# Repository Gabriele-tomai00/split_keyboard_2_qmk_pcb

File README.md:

# SPLIT KEYBOARD (my second version)

<!-- ## ⚠️ Report In Progress ⚠️ -->
This project details the design and construction of my first custom split keyboard. The build features a custom PCB, hand-soldered components, and a 3D-printed case, all powered by the Raspberry Pi Pico and QMK firmware.

**Key Features:**
- **Microcontroller**: Raspberry Pi Pico (RP2040)
- **Firmware**: QMK with Vial GUI support
- **Switches**: Hot-swappable MX switches
- **Displays**: OLED status screens
- **Input**: Rotary encoders
- **Interconnect**: RJ11 cabling for safe hot-plugging

The layout is a traditional row-staggered design (non-ortholinear) with ergonomic enhancements:
- **Inner Macro Keys**: 3 extra keys on the inner side of the right half.
- **Thumb Cluster**: 2 low-profile keys under each spacebar, primarily used as layer modifiers.

*Acknowledgments: Special thanks to the QMK and Vial communities, and the authors of the Sofle Pico keyboard, whose work provided invaluable inspiration and knowledge.*

## Repository Structure
- `/3d_images`: 3D design files (STL) created with Autodesk Fusion 360
- `/images`: Photographic documentation of the keyboard assembly and final build.
- `/kicad`: Electrical schematics and PCB layout designs developed in KiCad, ready for fabrication.
- `/vial-qmk`: Source code for the QMK-based firmware with Vial GUI support.
- `/vial_config.vil`: Vial configuration file (you can upload this file to Vial to configure the keyboard).
- `/perimeter_right.dxf` and `/perimeter_left.dxf`: DXF files for the right and left half PCB perimeter (used to cut the PCB).

## Components List
- Custom PCBs (Left & Right)
- 2x Raspberry Pi Pico
- 1N4148 Diodes
- Kailh Hot-swap Sockets
- SK6812MINI-E SMD LEDs
- EC11 Rotary Encoders
- 0.91" I2C OLED Displays
- RJ11 Jacks (6P6C or similar)
- Brass Standoffs (M2)

## Features & Implementation

### Layout & Ergonomics
The keyboard deviates slightly from a standard 60% ANSI layout to accommodate split ergonomics. It combines standard MX switches with low-profile switches for the thumb cluster to reduce strain. The extra macro keys on the left half provide quick access to custom functions.

### Software (QMK & Vial)
The keyboard runs on QMK firmware and is fully compatible with Vial. This allows for real-time configuration via a graphical interface without re-flashing. Users can program:
- **Layers**: Toggle between different keymaps (e.g., QWERTY, navigation, numpad).
- **Macros**: Automate complex key sequences.
- **Tap Dance**: Assign different actions to a key based on how many times it is tapped.

### Rotary Encoders (EC11)
The keyboard utilizes EC11 rotary encoders. In the QMK ecosystem, encoders provide a fluid input method distinct from binary key presses. They are ideal for continuous values like volume control, page scrolling, or history navigation.

### OLED Displays
Each half is equipped with an OLED display connected via the I2C protocol.

### RGB Backlighting (SK6812MINI-E)
The PCB features per-key RGB backlighting using SK6812MINI-E LEDs.
- **Technology**: These addressable "reverse-mount" LEDs sit within PCB cutouts, shining upwards through the switch housing.
- **Effects**: Powered by QMK's RGB Matrix system, the keyboard supports vast lighting animations, reactive typing effects, and layer-specific color coding (e.g., turning the keyboard red when on the "Function" layer).

## Hardware Details

### Microcontroller: Raspberry Pi Pico (RP2040)
I selected the Raspberry Pi Pico for this build due to its generous GPIO count compared to the Pro Micro. With 26 usable GPIO pins, the RP2040 handles the matrix, encoders, OLEDs, and RGB data lines directly, simplifying the PCB design.

### Split Connection: UART via RJ11
Communication between the two halves uses Full Duplex UART over an RJ11 cable (inspired by the Ultimate Hacking Keyboard).
- **Why RJ11?**: Unlike the common TRRS (Aux) cables used in many split keyboards, RJ11 connectors do not short pins momentarily during insertion or removal. This design choice eliminates the risk of shorting VCC to GND while the keyboard is powered.

I constructed a custom cable using 4-pin RJ11 connectors (6P4C) attached to a 4-core wire. It is crucial to ensure the connectors support at least 4 pins, avoiding the common 2-pin variants typically used for telephone lines in Italy.

### USB Type-C Connectivity
Each keyboard half features a dedicated USB Type-C port for computer connectivity. I chose this standard for its versatility and widespread adoption. The port is distinct from the inter-half connection to prevent accidental mismatches. Either half can be connected to the host computer.
I referenced the Raspberry Pi Pico datasheet to correctly wire the external USB-C breakout board to the microcontroller, ensuring the Pico detects the external connection as its primary USB interface.

### Key Matrix Wiring
QMK supports a key matrix configuration where each key is identified by a unique row-column combination, with diodes preventing ghosting (unwanted column activation).
The PCB and QMK firmware are configured as follows:

## 3D-Printed Case Design
I designed with Autodesk Fusion 360 and printed a custom enclosure using PLA. The chassis is modular, divided into multiple parts to:
- Allow for easy replacement of individual components without re-printing the entire case.
- Reduce print time per part (avoiding >20h single prints).

### 3D Printing Process
The enclosure components were manufactured using a Bambu Lab P1P 3D printer. While the design is compatible with standard printing profiles, a 0.2mm nozzle was utilized to achieve superior surface finish and precise detail resolution.
PLA (Polylactic Acid) was selected as the filament material due to its optimal balance of cost-effectiveness, printability, and mechanical durability suitable for this application.

### Assembly
The case uses threaded brass inserts (M2) for a robust and aesthetically pleasing assembly.

## Component Assembly & Soldering
All PCB components were hand-soldered, which included:
- **Raspberry Pi Pico**: Soldering all GPIO pins plus the two small test pads required for the external USB data lines.
- **Passive Components**: 2 capacitors per PCB.
- **Connectors**: External USB-C breakout (4 pins) and RJ11 jacks (4 pins).
- **Peripherals**: Rotary encoders (5 pins) and OLED display headers (4 pins).

For the matrix:
- **Diodes**: 1N4148 diodes for each key (2 points).
- **Sockets**: Kailh hot-swap sockets (2 points) - switches are not soldered directly.
- **LEDs**: SK6812MINI-E SMD LEDs (4 points per key).

A significant challenge was soldering the small voltage level shifter required for correct LED data signaling. As this was my first experience with soldering—especially with such small SMD components—the results are functional but reflect the learning curve involved.

## Flashing Instructions
1. Set up the **vial-qmk** environment by cloning the repository: [https://github.com/vial-kb/vial-qmk](https://github.com/vial-kb/vial-qmk).
2. Copy the `qmk-vial/new_split_keyboard_gabriele` directory from this project into the `vial-qmk/keyboards/` directory.
3. Flash the firmware using the following commands:

```bash
# Flash Left Side
qmk flash -kb new_split_keyboard_gabriele -km vial -bl uf2-split-left

# Flash Right Side
qmk flash -kb new_split_keyboard_gabriele -km vial -bl uf2-split-right
```

## Conclusions
Additional photographic documentation is available in the `/images` directory.

## References
- [QMK Firmware](https://qmk.fm/)
- [Raspberry Pi Pico Datasheet](https://datasheets.raspberrypi.com/pico/pico-datasheet.pdf)
- [Sofle Pico Split Keyboard](https://www.soflepico.com)
- [Ultimate Hacking Keyboard - blog](https://uhk.io/blog)
- [VIAL](https://blog.4dcu.be/diy/2023/12/03/pi-pico-usb-c.html)
- [Simple USB Type-C Upgrade for the Raspberry Pi Pico](https://blog.4dcu.be/diy/2023/12/03/pi-pico-usb-c.html)

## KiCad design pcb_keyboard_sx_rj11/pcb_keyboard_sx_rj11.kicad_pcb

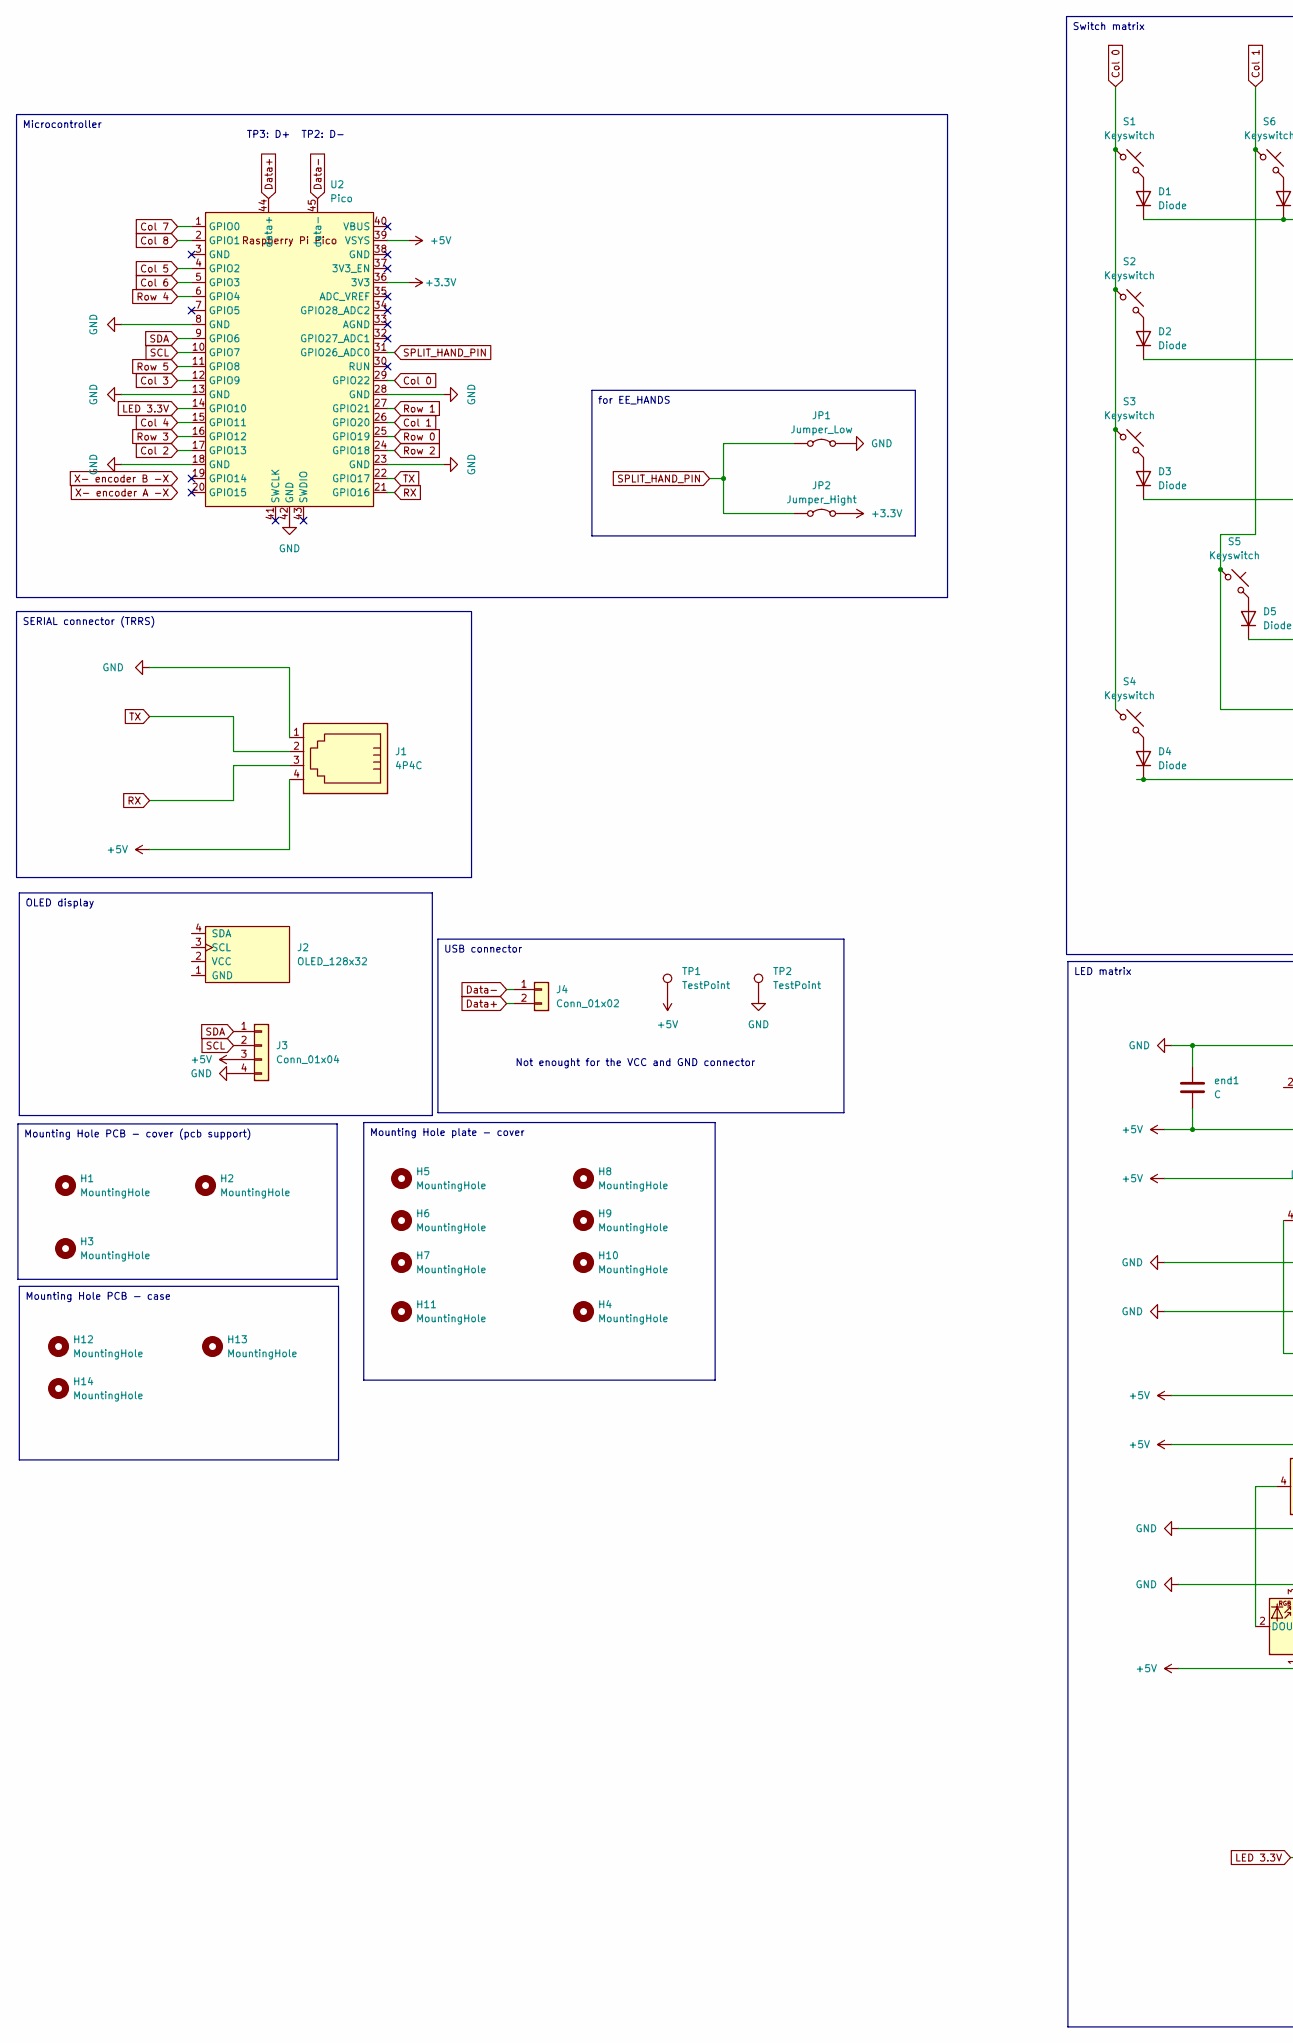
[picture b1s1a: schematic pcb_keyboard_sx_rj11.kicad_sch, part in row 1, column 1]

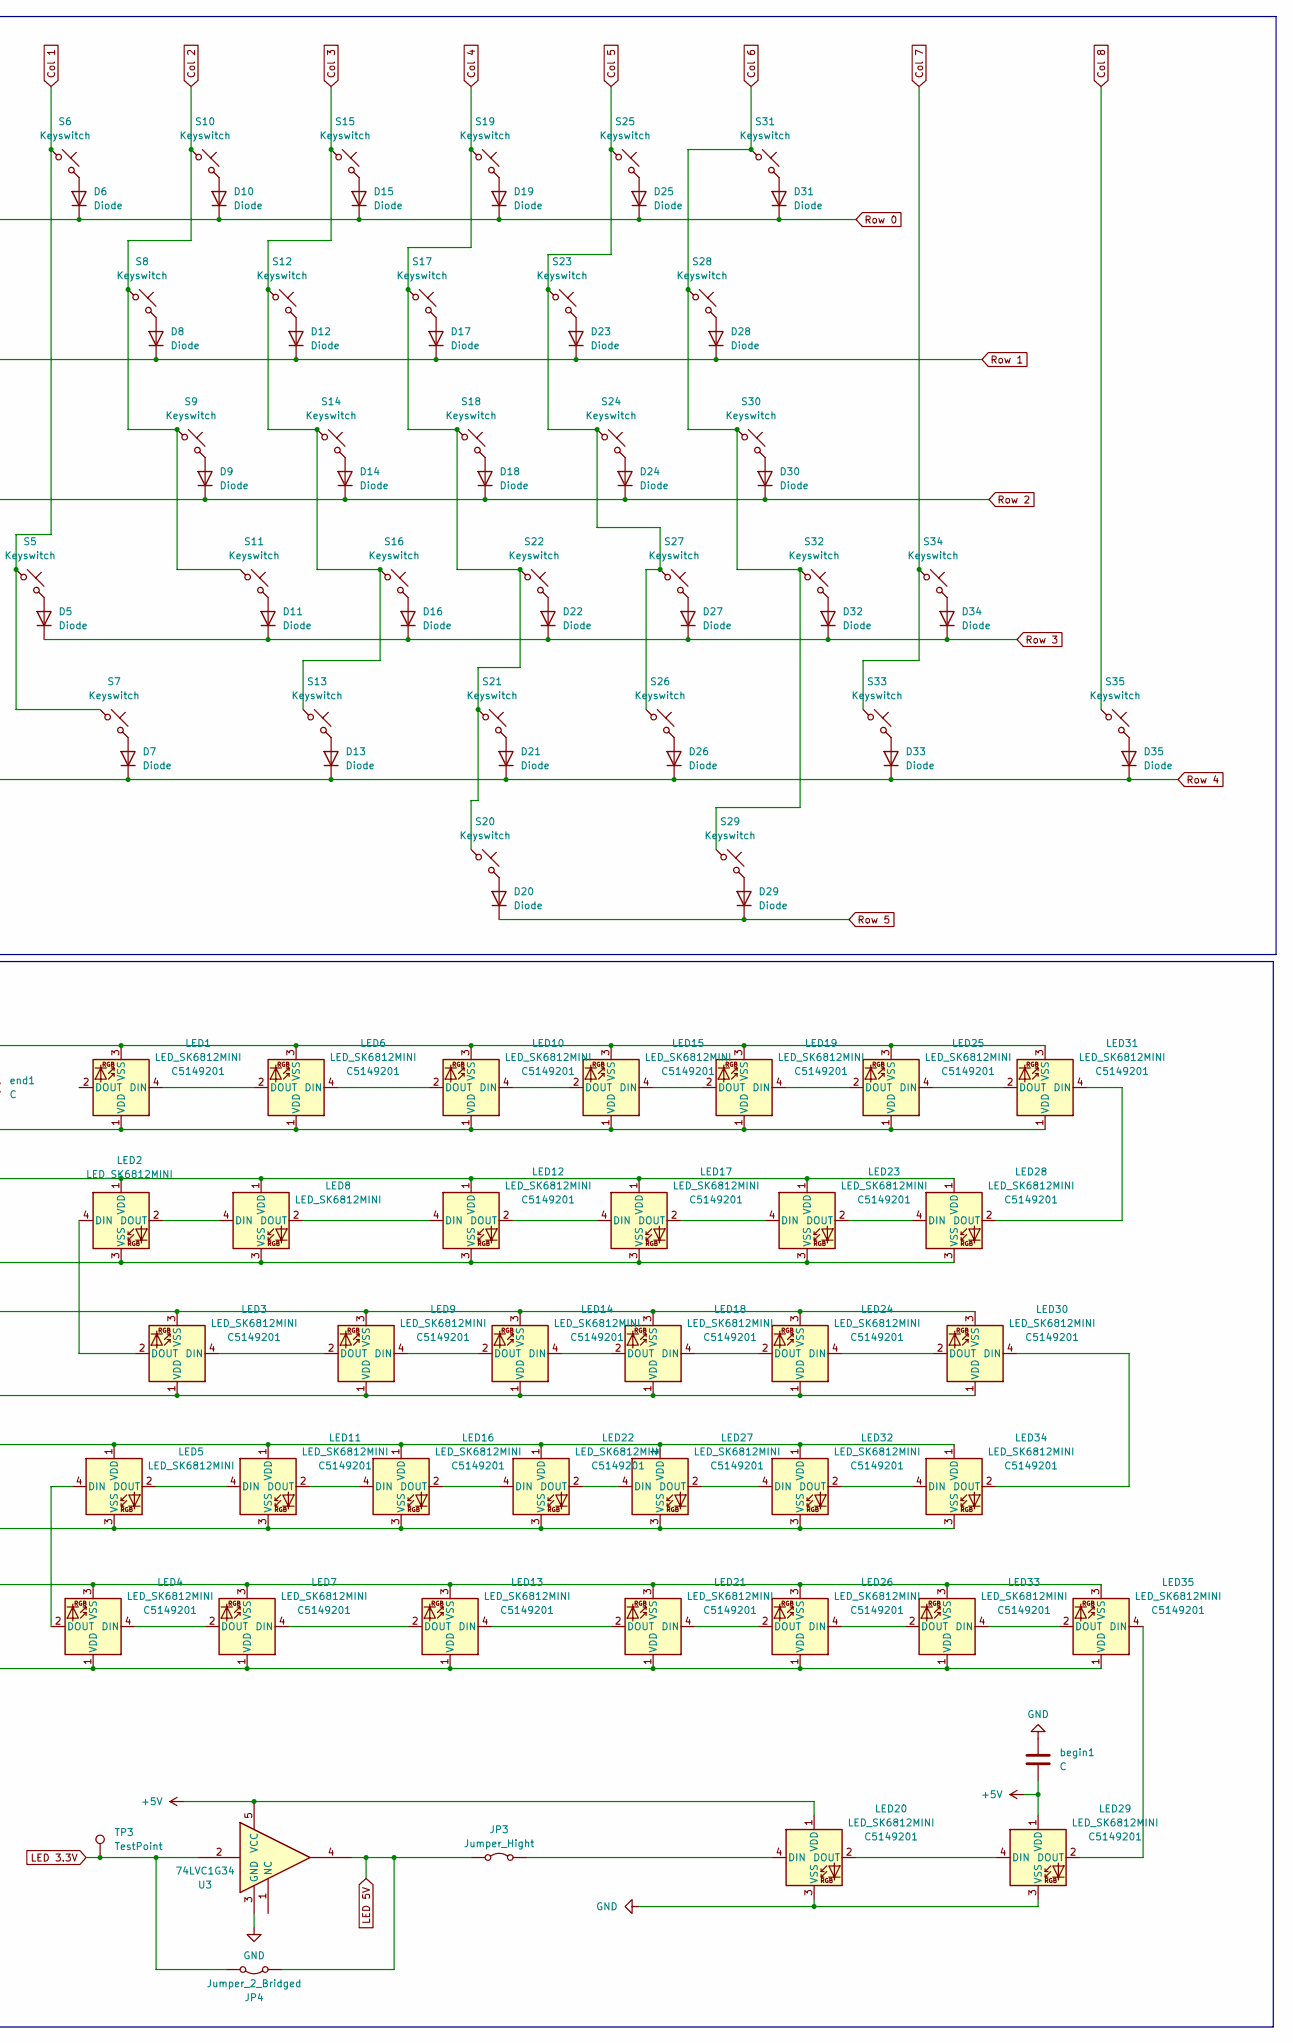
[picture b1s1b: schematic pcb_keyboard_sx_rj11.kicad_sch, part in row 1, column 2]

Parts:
D1, D2, D3, D4, D5, D6, D7, D8, D9, D10, D11, D12, D13, D14, D15, D16, D17, D18, D19, D20, D21, D22, D23, D24, D25, D26, D27, D28, D29, D30, D31, D32, D33, D34, D35: Diode; D_SOD-123_DO-35_Hybrid_DoubleSided_V2
H1, H2, H3: MountingHole; PCB_support_2.2mm_M2
H4, H5, H6, H7, H8, H9, H10, H11: MountingHole; MountingHole_3.2mm_M3
H12, H13, H14: MountingHole; MountingPCB_2.2mm_M2
J1: 4P4C; RJ12_Amphenol_54601-x06_Horizontal
J2: OLED_128x32
J3: Conn_01x04; PinHeader_1x04_P2.54mm_Horizontal
J4: Conn_01x02; PinHeader_1x02_P2.54mm_Horizontal
JP1: Jumper_Low; SolderJumper-2_P1.3mm_Bridged2Bar_Pad1.0x1.5mm
JP2, JP3: Jumper_Hight; SolderJumper-2_P1.3mm_Bridged2Bar_Pad1.0x1.5mm
JP4: Jumper_2_Bridged; SolderJumper-2_P1.3mm_Bridged2Bar_Pad1.0x1.5mm
LED1, LED2, LED3, LED4, LED5, LED6, LED7, LED8, LED9, LED10, LED11, LED12, LED13, LED14, LED15, LED16, LED17, LED18, LED19, LED20, LED21, LED22, LED23, LED24, LED25, LED26, LED27, LED28, LED29, LED30, LED31, LED32, LED33, LED34, LED35: LED_SK6812MINI; LCSC C5149201
S1, S6, S8, S9, S10, S11, S12, S14, S15, S16, S17, S18, S19, S22, S23, S24, S25, S27, S28, S30, S31, S32, S33, S34, S35: Keyswitch; Hotswap_MX_1.00u
S2: Keyswitch; Hotswap_MX_1.50u
S3, S26: Keyswitch; Hotswap_MX_1.75u
S4, S7, S13, S21: Keyswitch; Hotswap_MX_1.25u
S5: Keyswitch; Hotswap_MX_2.25u
S20: Keyswitch; Choc_V1_1.75u
S29: Keyswitch; Choc_V1_1.00u
TP1, TP2, TP3: TestPoint; PinHeader_1x01_P2.54mm_Vertical
U2: Pico; Raspberry_Pi_Pico_with_usb_rings
U3: 74LVC1G34; SOT-353_SC-70-5_Handsoldering
begin1: C; C_1812_4532Metric_Pad1.57x3.40mm_HandSolder
end1: C; C_1812_4532Metric_Pad1.57x3.40mm_HandSolder

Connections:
+3.3V: JP2.2 (B), U2.36 (3V3)
+5V: J1.4, J3.3, LED1.1 (VDD), LED2.1 (VDD), LED3.1 (VDD), LED4.1 (VDD), LED5.1 (VDD), LED6.1 (VDD), LED7.1 (VDD), LED8.1 (VDD), LED9.1 (VDD), LED10.1 (VDD), LED11.1 (VDD), LED12.1 (VDD), LED13.1 (VDD), LED14.1 (VDD), LED15.1 (VDD), LED16.1 (VDD), LED17.1 (VDD), LED18.1 (VDD), LED19.1 (VDD), LED20.1 (VDD), LED21.1 (VDD), LED22.1 (VDD), LED23.1 (VDD), LED24.1 (VDD), LED25.1 (VDD), LED26.1 (VDD), LED27.1 (VDD), LED28.1 (VDD), LED29.1 (VDD), LED30.1 (VDD), LED31.1 (VDD), LED32.1 (VDD), LED33.1 (VDD), LED34.1 (VDD), LED35.1 (VDD), TP1.1, U2.39 (VSYS), U3.5 (VCC), begin1.1, end1.1
Col 0: S1.1, S2.1, S3.1, S4.1, U2.29 (GPIO22)
Col 1: S5.1, S6.1, S7.1, U2.26 (GPIO20)
Col 2: S8.1, S9.1, S10.1, S11.1, U2.17 (GPIO13)
Col 3: S12.1, S13.1, S14.1, S15.1, S16.1, U2.12 (GPIO9)
Col 4: S17.1, S18.1, S19.1, S20.1, S21.1, S22.1, U2.15 (GPIO11)
Col 5: S23.1, S24.1, S25.1, S26.1, S27.1, U2.4 (GPIO2)
Col 6: S28.1, S29.1, S30.1, S31.1, S32.1, U2.5 (GPIO3)
Col 7: S33.1, S34.1, U2.1 (GPIO0)
Col 8: S35.1, U2.2 (GPIO1)
Data+: J4.2, U2.44 (data+)
Data-: J4.1, U2.45 (data-)
GND: J1.1, J3.4, JP1.2 (B), LED1.3 (VSS), LED2.3 (VSS), LED3.3 (VSS), LED4.3 (VSS), LED5.3 (VSS), LED6.3 (VSS), LED7.3 (VSS), LED8.3 (VSS), LED9.3 (VSS), LED10.3 (VSS), LED11.3 (VSS), LED12.3 (VSS), LED13.3 (VSS), LED14.3 (VSS), LED15.3 (VSS), LED16.3 (VSS), LED17.3 (VSS), LED18.3 (VSS), LED19.3 (VSS), LED20.3 (VSS), LED21.3 (VSS), LED22.3 (VSS), LED23.3 (VSS), LED24.3 (VSS), LED25.3 (VSS), LED26.3 (VSS), LED27.3 (VSS), LED28.3 (VSS), LED29.3 (VSS), LED30.3 (VSS), LED31.3 (VSS), LED32.3 (VSS), LED33.3 (VSS), LED34.3 (VSS), LED35.3 (VSS), TP2.1, U2.8 (GND), U2.13 (GND), U2.18 (GND), U2.23 (GND), U2.28 (GND), U2.42 (GND), U3.3 (GND), begin1.2, end1.2
LED 3.3V: JP4.2 (B), TP3.1, U2.14 (GPIO10), U3.2
LED 5V: JP3.1 (A), JP4.1 (A), U3.4
unnamed: D1.2 (A), S1.2
unnamed: D2.2 (A), S2.2
unnamed: D3.2 (A), S3.2
unnamed: D4.2 (A), S4.2
unnamed: D5.2 (A), S5.2
unnamed: D6.2 (A), S6.2
unnamed: D7.2 (A), S7.2
unnamed: D8.2 (A), S8.2
unnamed: D9.2 (A), S9.2
unnamed: D10.2 (A), S10.2
unnamed: D11.2 (A), S11.2
unnamed: D12.2 (A), S12.2
unnamed: D13.2 (A), S13.2
unnamed: D14.2 (A), S14.2
unnamed: D15.2 (A), S15.2
unnamed: D16.2 (A), S16.2
unnamed: D17.2 (A), S17.2
unnamed: D18.2 (A), S18.2
unnamed: D19.2 (A), S19.2
unnamed: D20.2 (A), S20.2
unnamed: D21.2 (A), S21.2
unnamed: D22.2 (A), S22.2
unnamed: D23.2 (A), S23.2
unnamed: D24.2 (A), S24.2
unnamed: D25.2 (A), S25.2
unnamed: D26.2 (A), S26.2
unnamed: D27.2 (A), S27.2
unnamed: D28.2 (A), S28.2
unnamed: D29.2 (A), S29.2
unnamed: D30.2 (A), S30.2
unnamed: D31.2 (A), S31.2
unnamed: D32.2 (A), S32.2
unnamed: D33.2 (A), S33.2
unnamed: D34.2 (A), S34.2
unnamed: D35.2 (A), S35.2
unnamed: JP3.2 (B), LED20.4 (DIN)
unnamed: LED1.4 (DIN), LED6.2 (DOUT)
unnamed: LED2.4 (DIN), LED3.2 (DOUT)
unnamed: LED2.2 (DOUT), LED8.4 (DIN)
unnamed: LED3.4 (DIN), LED9.2 (DOUT)
unnamed: LED4.4 (DIN), LED7.2 (DOUT)
unnamed: LED4.2 (DOUT), LED5.4 (DIN)
unnamed: LED10.4 (DIN), LED15.2 (DOUT)
unnamed: LED6.4 (DIN), LED10.2 (DOUT)
unnamed: LED5.2 (DOUT), LED11.4 (DIN)
unnamed: LED11.2 (DOUT), LED16.4 (DIN)
unnamed: LED8.2 (DOUT), LED12.4 (DIN)
unnamed: LED12.2 (DOUT), LED17.4 (DIN)
unnamed: LED13.4 (DIN), LED21.2 (DOUT)
unnamed: LED7.4 (DIN), LED13.2 (DOUT)
unnamed: LED14.4 (DIN), LED18.2 (DOUT)
unnamed: LED9.4 (DIN), LED14.2 (DOUT)
unnamed: LED15.4 (DIN), LED19.2 (DOUT)
unnamed: LED16.2 (DOUT), LED22.4 (DIN)
unnamed: LED17.2 (DOUT), LED23.4 (DIN)
unnamed: LED18.4 (DIN), LED24.2 (DOUT)
unnamed: LED19.4 (DIN), LED25.2 (DOUT)
unnamed: LED20.2 (DOUT), LED29.4 (DIN)
unnamed: LED21.4 (DIN), LED26.2 (DOUT)
unnamed: LED22.2 (DOUT), LED27.4 (DIN)
unnamed: LED23.2 (DOUT), LED28.4 (DIN)
unnamed: LED24.4 (DIN), LED30.2 (DOUT)
unnamed: LED25.4 (DIN), LED31.2 (DOUT)
unnamed: LED26.4 (DIN), LED33.2 (DOUT)
unnamed: LED27.2 (DOUT), LED32.4 (DIN)
unnamed: LED28.2 (DOUT), LED31.4 (DIN)
unnamed: LED29.2 (DOUT), LED35.4 (DIN)
unnamed: LED30.4 (DIN), LED34.2 (DOUT)
unnamed: LED32.2 (DOUT), LED34.4 (DIN)
unnamed: LED33.4 (DIN), LED35.2 (DOUT)
RX: J1.3, U2.21 (GPIO16)
Row 0: D1.1 (K), D6.1 (K), D10.1 (K), D15.1 (K), D19.1 (K), D25.1 (K), D31.1 (K), U2.25 (GPIO19)
Row 1: D2.1 (K), D8.1 (K), D12.1 (K), D17.1 (K), D23.1 (K), D28.1 (K), U2.27 (GPIO21)
Row 2: D3.1 (K), D9.1 (K), D14.1 (K), D18.1 (K), D24.1 (K), D30.1 (K), U2.24 (GPIO18)
Row 3: D5.1 (K), D11.1 (K), D16.1 (K), D22.1 (K), D27.1 (K), D32.1 (K), D34.1 (K), U2.16 (GPIO12)
Row 4: D4.1 (K), D7.1 (K), D13.1 (K), D21.1 (K), D26.1 (K), D33.1 (K), D35.1 (K), U2.6 (GPIO4)
Row 5: D20.1 (K), D29.1 (K), U2.11 (GPIO8)
SCL: J3.2, U2.10 (GPIO7)
SDA: J3.1, U2.9 (GPIO6)
SPLIT_HAND_PIN: JP1.1 (A), JP2.1 (A), U2.31 (GPIO26_ADC0)
TX: J1.2, U2.22 (GPIO17)

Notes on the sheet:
Switch matrix
USB connector
for EE_HANDS
SERIAL connector (TRRS)
Mounting Hole PCB - case
LED matrix
Mounting Hole plate - cover
Mounting Hole PCB - cover (pcb support)
Microcontroller
OLED display
TP3: D+
Not enought for the VCC and GND connector
TP2: D-

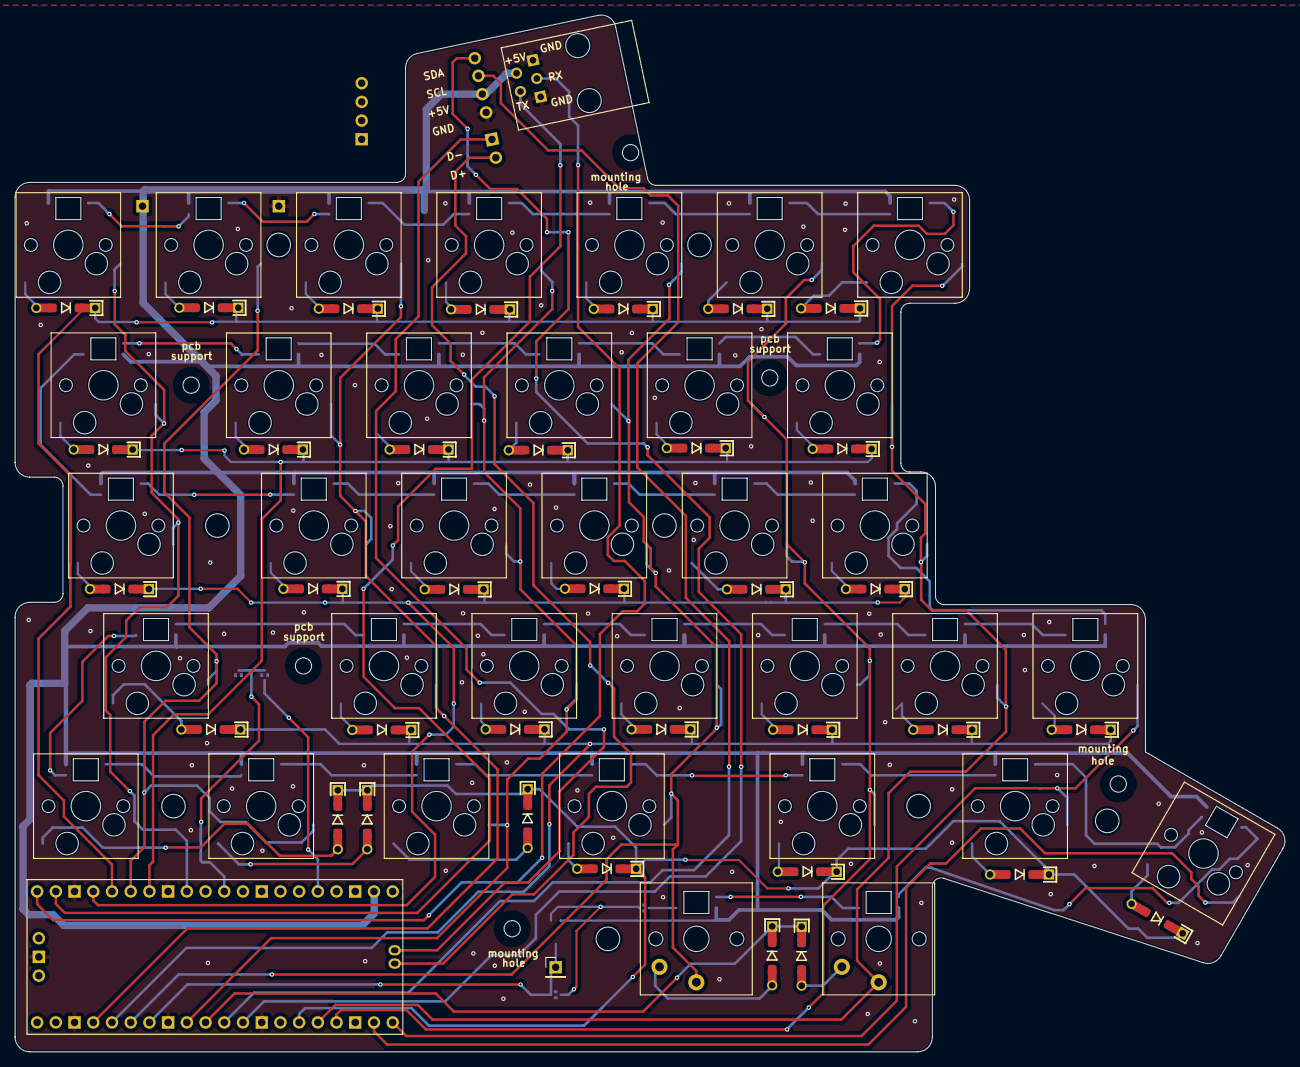
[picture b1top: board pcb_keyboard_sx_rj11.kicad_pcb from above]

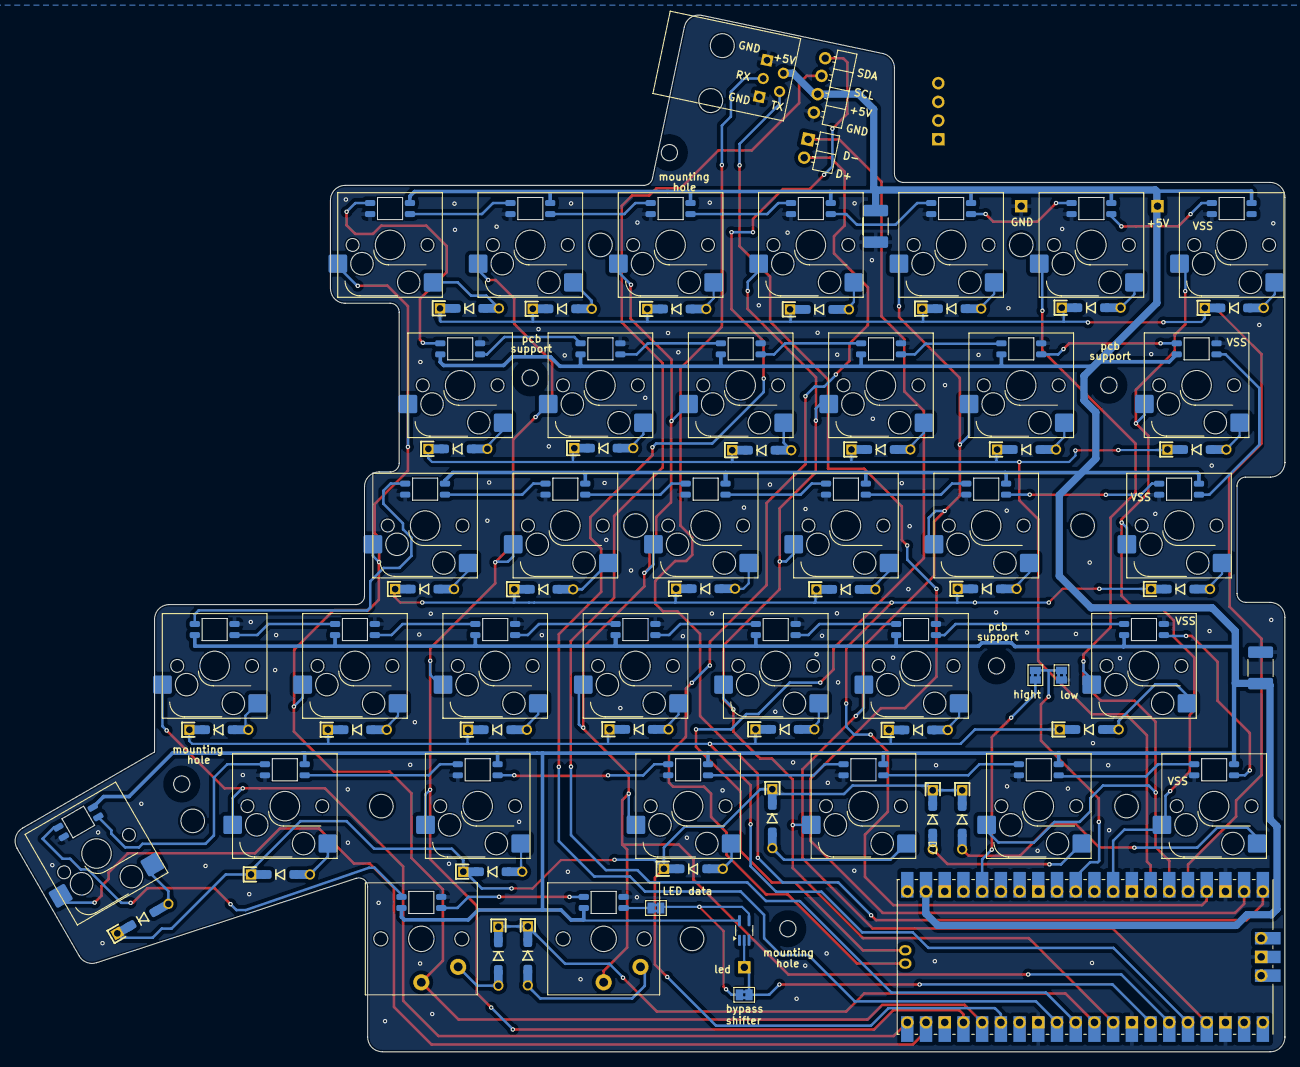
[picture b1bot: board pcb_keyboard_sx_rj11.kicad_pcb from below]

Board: 2 copper layers, 172.3 x 140.7 mm, 134 parts (79 on the bottom side), 97 nets.
